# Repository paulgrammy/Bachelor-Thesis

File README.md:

# Bachelor-Thesis

## Introduction and motivation
In recent years, there has been a growing emphasis on learning through hands-on experimentation, particularly in engineering education. One effective way to explore the behavior of electrical components is by using sound signals, which provide an intuitive and immediate way to observe phenomena such as filtering and waveshaping. \newline

My body of work builds on my prior student research project that exemplified this approach using filters. In the project, a prototype was built that takes Bluetooth audio from a source and feeds it through filters studied in electronics labs, thus enabling a better understanding of signal processing concepts. The board then passes the resulting sound to an audio device such as headphones or speakers.

## Requirements and considerations
System-wise, the board shall take +15 V and step it down to supply voltages required by each IC. A 2-layered design is shown, featuring four mounting pins for FestoBoard compatibility. Below, a block diagram is shown, underlying the ICs used for my implementation:

## Physical view
SMD components alongside SOIC packages for ICs have been used to allow space for all components. Alongside passives and ICs, some buttons and LEDs have been added for user interaction. These shall be handled by the ESP32:

## Software
The ESP32 found on the PCB acts as either:
1) A Bluetooth receiver using [pschatzmann's A2DP library](https://github.com/pschatzmann/ESP32-A2DP);
2) A waveform generator, interfacing via I2S with the DAC to output one of four different waveforms.

FreeRTOS tasks are used to handle the different states of the code:

## Repo structure
* doc: Pictures, Datasheets, Files documenting different aspects of the project
* footprints: different footprints used in the PCB layout
* schematics: KiCAD schematic and layout, and the LTSpice simulation of Op-Amp stages can be found here
* software: the code implementation

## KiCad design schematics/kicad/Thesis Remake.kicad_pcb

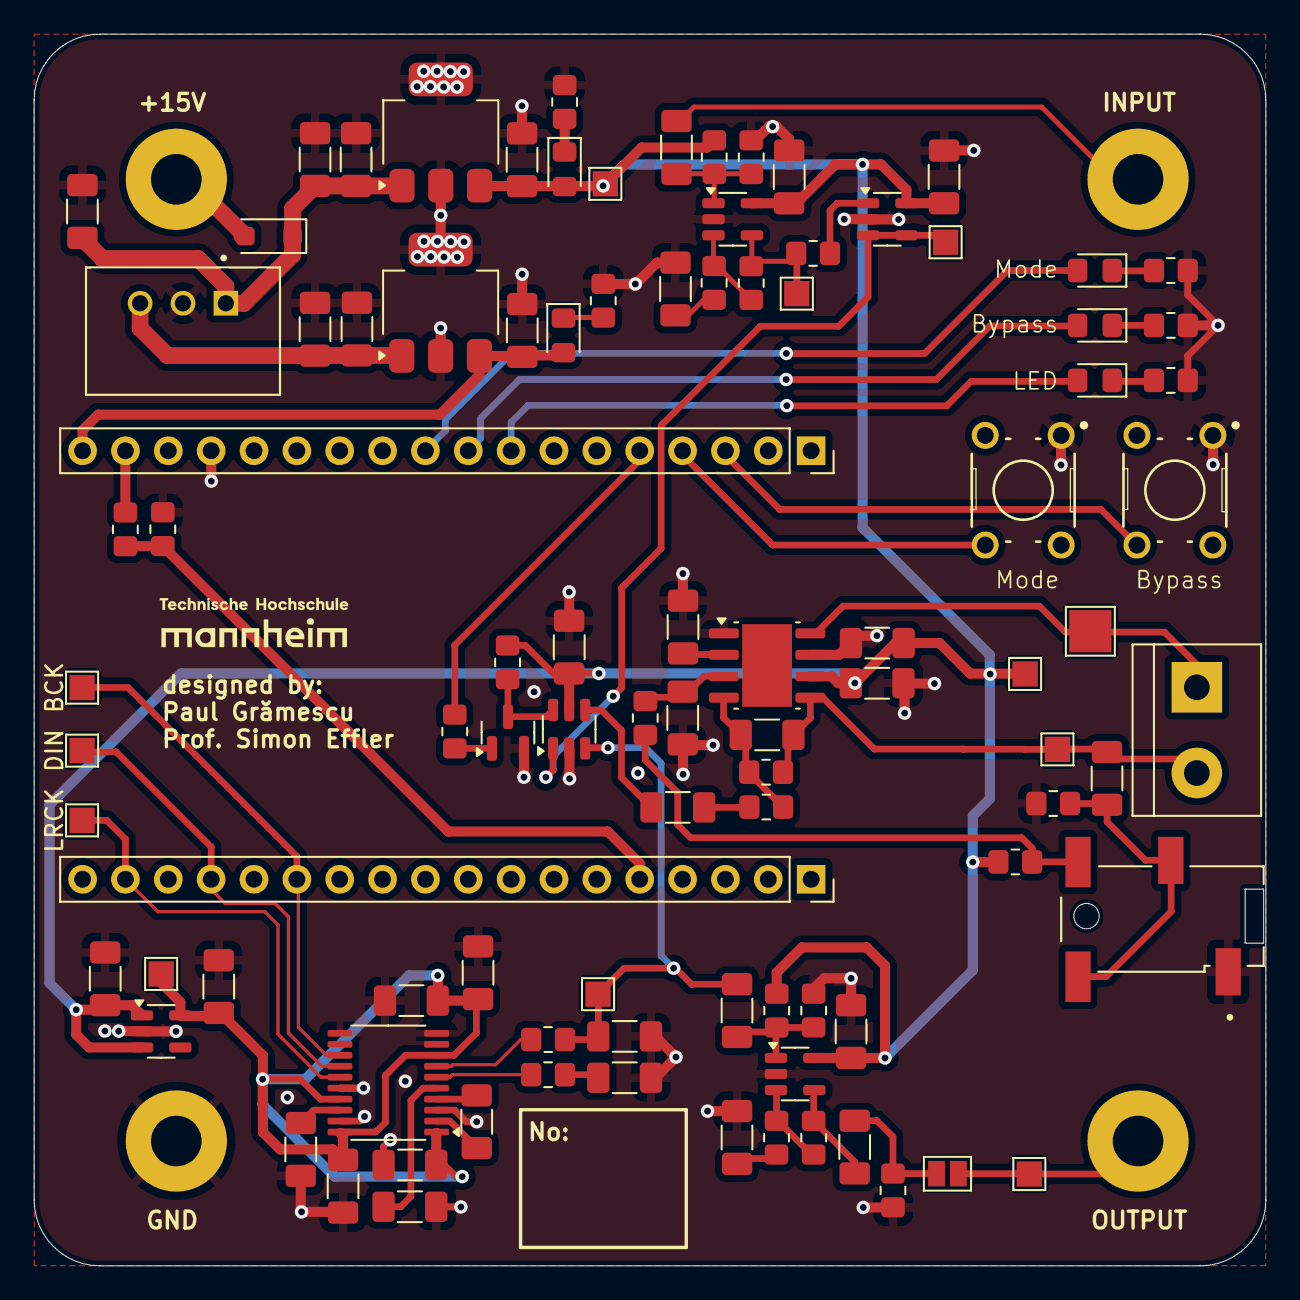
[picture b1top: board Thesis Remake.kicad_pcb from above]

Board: 2 copper layers, 73.0 x 73.0 mm, 100 parts (0 on the bottom side), 55 nets.

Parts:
+5V1: TestPoint; TestPoint_Pad_1.5x1.5mm
BCK: TestPoint; TestPoint_Pad_1.5x1.5mm
BUFFER_OUT1: TestPoint; TestPoint_Pad_1.5x1.5mm
C1, C4, C11, C17, C19, C20, C21, C24, C27, C30, C34: 10uF; C_1206_3216Metric_Pad1.33x1.80mm_HandSolder
C2, C5, C33: 0.47uF; C_1206_3216Metric_Pad1.33x1.80mm_HandSolder
C3, C6, C8: 22uF; C_1206_3216Metric_Pad1.33x1.80mm_HandSolder
C7: 1uF; C_1206_3216Metric_Pad1.33x1.80mm_HandSolder
C9, C10: 2.2nF; C_1206_3216Metric_Pad1.33x1.80mm_HandSolder
C12, C13, C15, C16, C26, C28: 0.1uF; C_1206_3216Metric_Pad1.33x1.80mm_HandSolder
C14, C25, C32: 2.2uF; C_1206_3216Metric_Pad1.33x1.80mm_HandSolder
C18, C22, C23, C31: 10nF; C_1206_3216Metric_Pad1.33x1.80mm_HandSolder
C29: 5pF; C_1206_3216Metric_Pad1.33x1.80mm_HandSolder
D5: D_Schottky; D_SOD-123F
D7, D8, D9, D10, D11: LED; LED_0805_2012Metric_Pad1.15x1.40mm_HandSolder
DEBUG1: 0; R_0805_2012Metric_Pad1.20x1.40mm_HandSolder
DIN: TestPoint; TestPoint_Pad_1.5x1.5mm
J1: SJ2-35853B-SMT-TR; CUI_SJ2-35853B-SMT-TR
J2, J3: Conn_01x18; PinSocket_1x18_P2.54mm_Vertical
J4, J5, J6, J7: Conn_01x01_Pin; FestoBoard_Drill_Hole
JP3: Jumper_2_Open; SolderJumper-2_P1.3mm_Open_Pad1.0x1.5mm
LRCK: TestPoint; TestPoint_Pad_1.5x1.5mm
LS1: Speaker; TerminalBlock_bornier-2_P5.08mm
OUTPUT_AS1, OUTPUT_AS2: TestPoint; TestPoint_Pad_1.5x1.5mm
OUT_DAC_R1: TestPoint; TestPoint_Pad_1.5x1.5mm
PS1: TSR_0.5-2465; CONV_TSR_0.5-2465
Q1: MMBT7002K; SOT-23
R1, R2: 330; R_0805_2012Metric_Pad1.20x1.40mm_HandSolder
R3, R4, R20: 470; R_0805_2012Metric_Pad1.20x1.40mm_HandSolder
R5, R6, R10, R11, R17: 10K; R_0805_2012Metric_Pad1.20x1.40mm_HandSolder
R7: 100k; R_0805_2012Metric_Pad1.20x1.40mm_HandSolder
R8, R13, R19: 5K; R_0805_2012Metric_Pad1.20x1.40mm_HandSolder
R9, R12, R14, R15: 100K; R_0805_2012Metric_Pad1.20x1.40mm_HandSolder
R16: 50k; R_0805_2012Metric_Pad1.20x1.40mm_HandSolder
R18: 1K; R_0805_2012Metric_Pad1.20x1.40mm_HandSolder
R21, R22: 1k; R_0805_2012Metric_Pad1.20x1.40mm_HandSolder
R23, R24, R25: 2.2K; R_0805_2012Metric_Pad1.20x1.40mm_HandSolder
S1, S2: B3F-1000; SW_B3F-1000
TP_VDD_TPA1: TestPoint; TestPoint_Pad_1.5x1.5mm
U2: PCM5102; TSSOP-20_4.4x6.5mm_P0.65mm
U3: SN74LVC1G3157; SOT-23-6
U5: RT9080-33GJ5; SOT-23-5
U6, U8: LM2940CT-5.0_MOD; SOT-223
U7: TPA711; Texas_R-PDSO-G8_EP2.95x4.9mm_Mask2.4x3.1mm
U9, U10, U11: MCP6001-OT; SOT-23-5
VDD1: TestPoint; TestPoint_Pad_1.5x1.5mm
Vo+1: TestPoint; TestPoint_Pad_1.5x1.5mm
Vo-1: TestPoint; TestPoint_Pad_2.5x2.5mm

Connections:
+3v3: C8.2, C11.1, C12.2, C13.2, C15.2, U2.1 (CPVDD), U2.8 (AVDD), U2.17 (XSMT), U2.20 (DVDD), U5.5 (VOUT), VDD1.1
+3v3_ESP: J2.17, R21.2
+5V: +5V1.1, C3.2, C7.2, C18.2, C22.2, C23.2, C27.1, C28.1, C31.1, D10.2 (A), R5.2, R10.2, R15.2, R19.2, TP_VDD_TPA1.1, U3.5 (+), U5.1 (VIN), U5.3 (EN), U7.6 (V_{DD}), U8.3 (OUT), U9.5 (V+), U10.5 (V+), U11.5 (V+)
+5V1: C6.2, D11.2 (A), J2.18, U6.3 (OUT)
+6.5V: C4.1, C5.2, PS1.3 (+VOUT), U6.1 (IN)
+15V: D5.2 (A), J5.1
+15V_Diode: C1.1, C2.2, C34.1, D5.1 (K), PS1.1 (+VIN), U8.1 (IN)
/ADC: J3.5, R21.1, R22.1
/BCK: BCK.1, J3.13, U2.13 (BCK)
/BUFFEROUT: BUFFER_OUT1.1, U3.1 (B), U11.3 (-), U11.4
/Bypass: C33.2, U3.4 (C)
/DIN: DIN.1, J3.15, U2.14 (DIN)
/Filter_IN: J7.1, JP3.2 (B), OUTPUT_AS1.1
/Filter_OUT: C21.1, J6.1
/HI_LO: J2.5, R20.1
/IN: C29.1, R16.2, R17.2, U7.4 (IN)
/LDOO: C16.1, U2.18 (LDOO)
/LED_1: D7.2 (A), J2.8
/LED_2: D8.2 (A), J2.9
/LED_3: D9.2 (A), J2.10
/LRCK: J3.17, LRCK.1, U2.15 (LRCK)
/OUTDACL: C9.1, R3.2
/OUTDACR: C10.1, C17.1, OUT_DAC_R1.1, R4.2, U3.3 (A)
/Poll_Button_1: J2.4, S1.4
/Poll_Button_2: J2.3, S2.4
/SE/~BTL: J1.10, R14.1, R15.1
/VNEG: C14.2, U2.5 (VNEG)
/Vo+: C29.2, C30.1, LS1.2, R16.1, U7.5 (V_{O+}), Vo+1.1
/Vo-: LS1.1, U7.8 (V_{O-}), Vo-1.1
GND: C1.2, C2.1, C3.1, C4.2, C5.1, C6.1, C7.1, C8.1, C9.2, C10.2, C11.2, C12.1, C13.1, C14.1, C15.1, C16.2, C18.1, C20.1, C22.1, C23.1, C24.1, C25.2, C26.2, C27.2, C28.2, C31.2, C34.2, J1.1, J2.15, J4.1, PS1.2 (GND), Q1.2, R1.1, R2.1, R6.2, R9.1, R11.2, R18.2, R22.2, R23.1, R24.1, R25.1, S1.1, S2.1, U2.3 (CPGND), U2.9 (AGND), U2.10 (DEMP), U2.11 (FLT), U2.16 (FMT), U2.19 (DGND), U3.2 (-), U5.2 (GND), U6.2 (GND), U6.4 (GND), U7.1 (SHUTDOWN), U7.7 (GND), U8.2 (GND), U8.4 (GND), U9.2 (V-), U10.2 (V-), U11.2 (V-)
unnamed: C19.2, R8.2, U9.4
unnamed: C20.2, R7.1
unnamed: C24.2, R12.1
unnamed: C30.2, J1.2, J1.3, R18.1
unnamed: C33.1, R17.1
unnamed: D7.1 (K), R23.2
unnamed: D8.1 (K), R24.2
unnamed: D9.1 (K), R25.2
unnamed: D10.1 (K), R1.2
unnamed: D11.1 (K), R2.2
unnamed: DEBUG1.1, OUTPUT_AS2.1, R13.2, U10.4
unnamed: C19.1, JP3.1 (A), R9.2
unnamed: Q1.1, R20.2
unnamed: C32.2, U2.4 (CAPM)
unnamed: C32.1, U2.2 (CAPP)
unnamed: R3.1, U2.6 (OUTL)
unnamed: R4.1, U2.7 (OUTR)
unnamed: Q1.3, R19.1, U3.6 (S)
unnamed: C25.1, U7.2 (BYPASS)
unnamed: C26.1, R14.2, U7.3 (SE/~BTL)
unnamed: C17.2, R5.1, R6.1, U9.1 (+)
unnamed: R7.2, R8.1, U9.3 (-)
unnamed: C21.2, R10.1, R11.1, U10.1 (+)
unnamed: R12.2, R13.1, U10.3 (-)
unnamed: DEBUG1.2, U11.1 (+)

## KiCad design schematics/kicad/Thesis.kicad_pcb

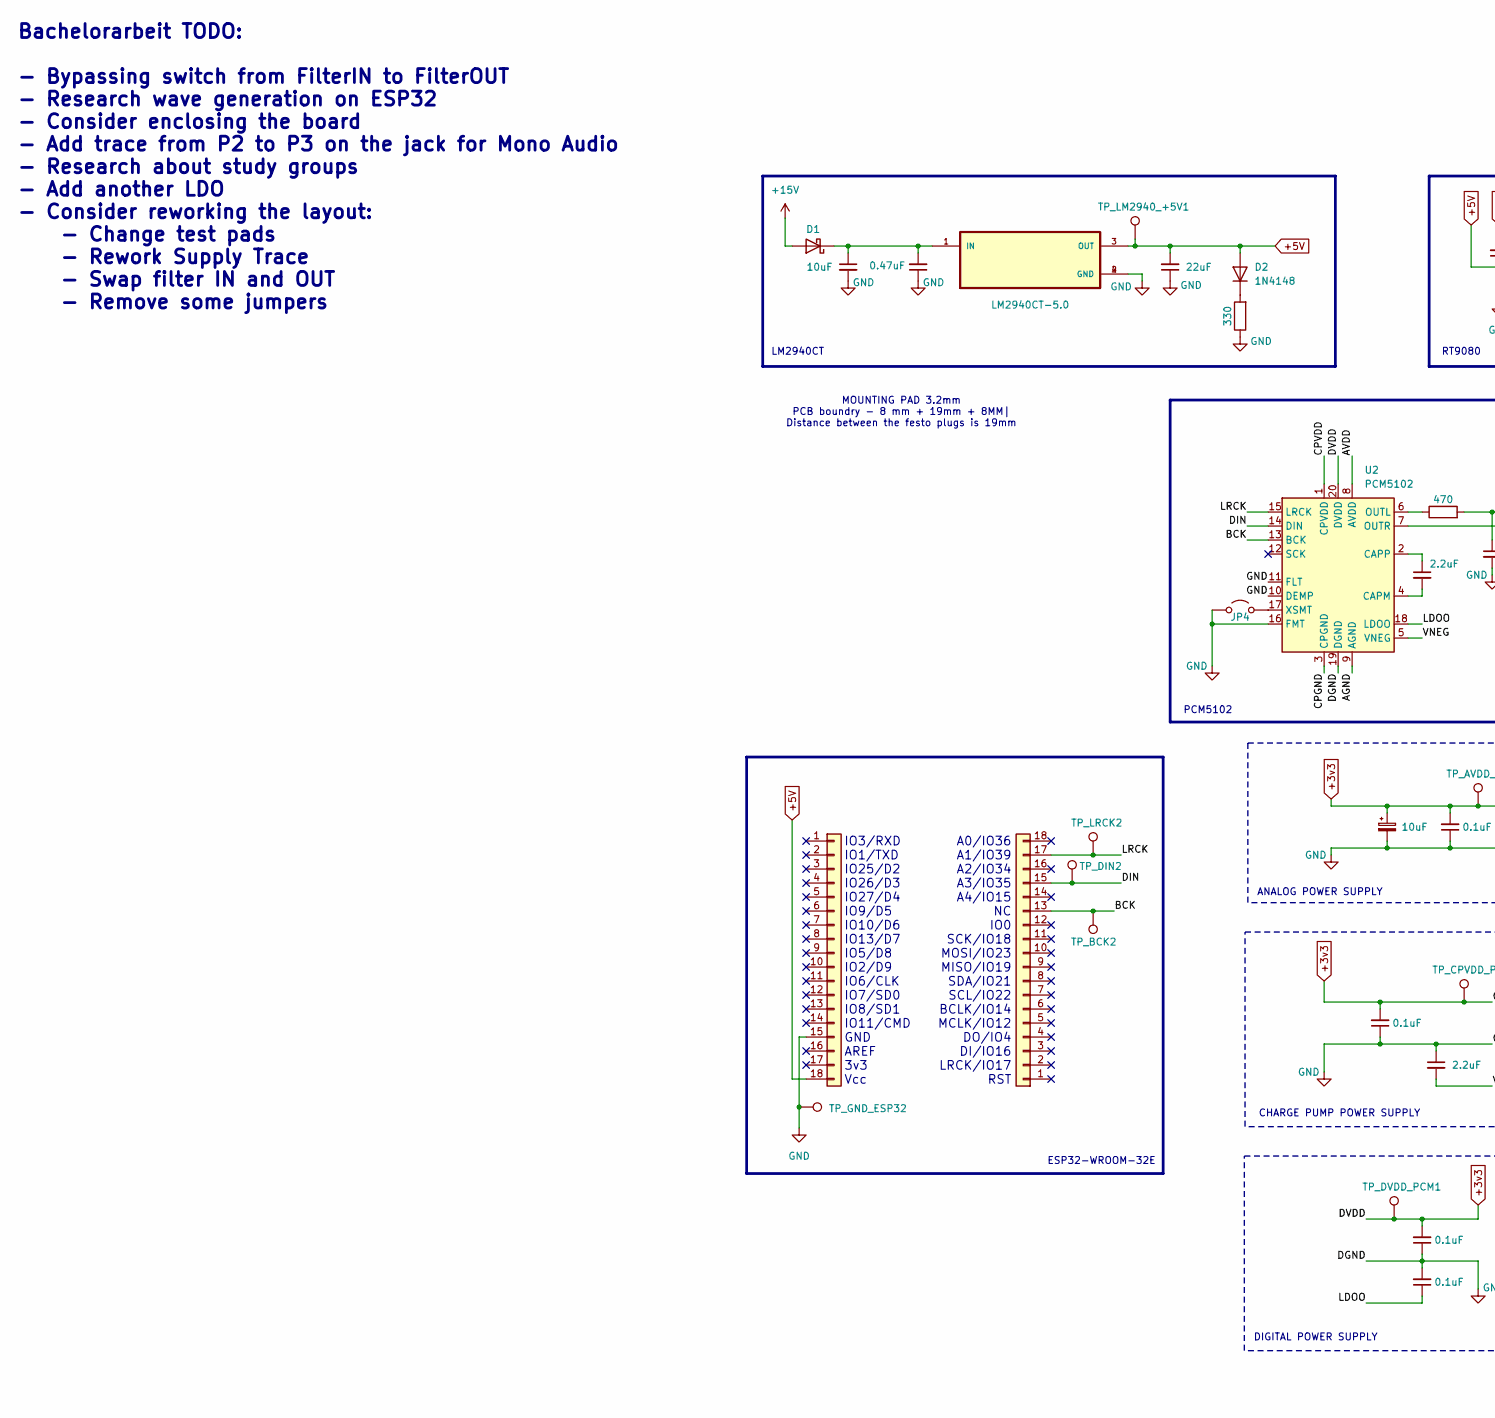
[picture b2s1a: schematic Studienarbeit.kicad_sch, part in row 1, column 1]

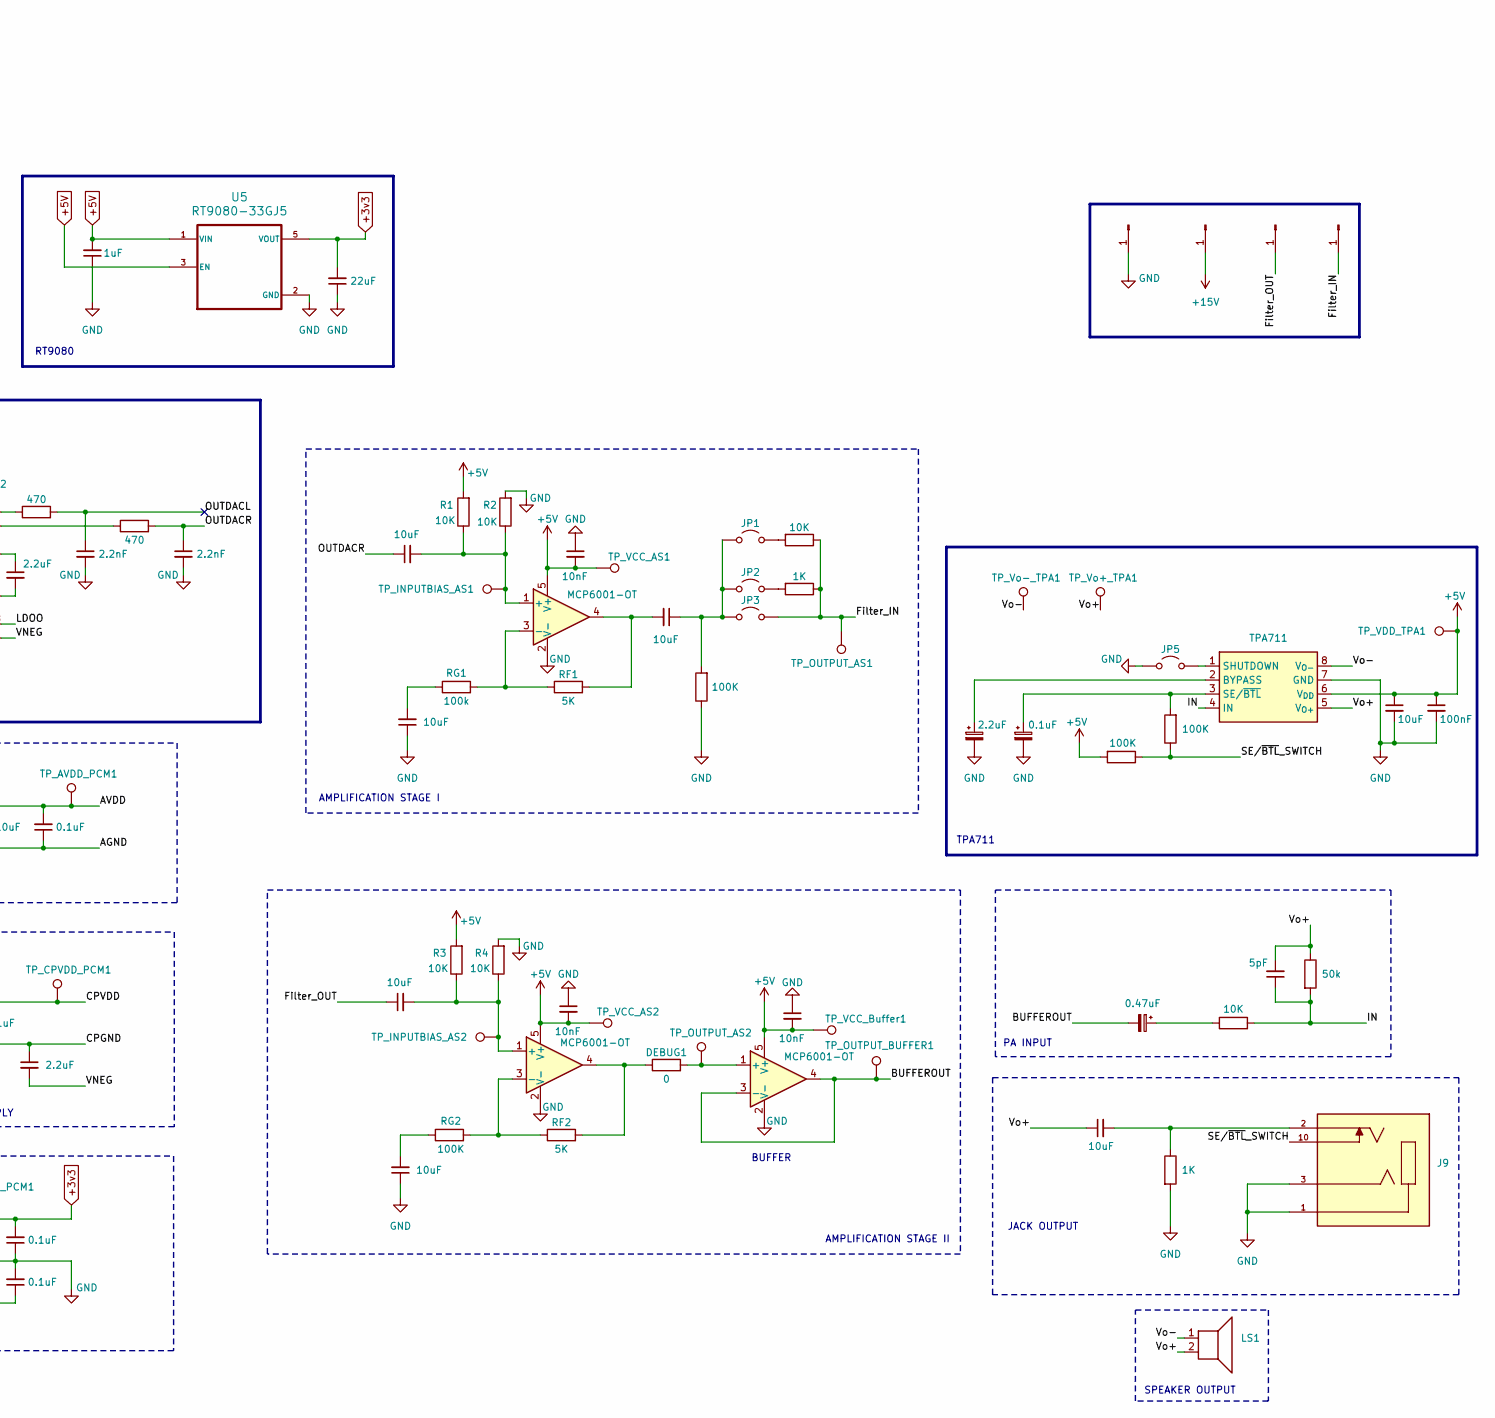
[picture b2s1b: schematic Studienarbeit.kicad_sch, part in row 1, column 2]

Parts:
C1_APS_PCM5102: 10uF; C_1206_3216Metric_Pad1.33x1.80mm_HandSolder
C1_CPPS_PCM1, C1_DPS_PCM1, C2_APS_PCM5102, C2_DPS_PCM1: 0.1uF; C_1206_3216Metric_Pad1.33x1.80mm_HandSolder
C2_CPPS_PCM1: 2.2uF; C_1206_3216Metric_Pad1.33x1.80mm_HandSolder
CA_PCM5102: 2.2uF; C_1206_3216Metric_Pad1.33x1.80mm_HandSolder
CB_TPA1: 2.2uF; C_1206_3216Metric_Pad1.33x1.80mm_HandSolder
CF_TPA711: 5pF; C_1206_3216Metric_Pad1.33x1.80mm_HandSolder
CG1_PCM5102, CG2_PCM5102: 2.2nF; C_1206_3216Metric_Pad1.33x1.80mm_HandSolder
CI_TPA711: 0.47uF; C_1206_3216Metric_Pad1.33x1.80mm_HandSolder
C_COUPLING_AMPSTAGE1: 10uF; C_1206_3216Metric_Pad1.33x1.80mm_HandSolder
C_COUPLING_AMPSTAGE2, C_COUPLING_AMPSTAGE3, C_COUPLING_AMPSTAGE4: 10nF; C_1206_3216Metric_Pad1.33x1.80mm_HandSolder
C_GND_AMPSTAGE1, C_GND_AMPSTAGE2, C_GND_AMPSTAGE3: 10uF; C_1206_3216Metric_Pad1.33x1.80mm_HandSolder
C_INPUT_LDO1: 0.47uF; C_1206_3216Metric_Pad1.33x1.80mm_HandSolder
C_INPUT_RT1: 22uF; C_1206_3216Metric_Pad1.33x1.80mm_HandSolder
C_INPUT_RT9080: 1uF; C_1206_3216Metric_Pad1.33x1.80mm_HandSolder
C_INPUT_TPA1, C_INPUT_TPA3: 10uF; C_1206_3216Metric_Pad1.33x1.80mm_HandSolder
C_INPUT_TPA2: 100nF; C_1206_3216Metric_Pad1.33x1.80mm_HandSolder
C_IN_+15V_1: 10uF; C_1206_3216Metric_Pad1.33x1.80mm_HandSolder
C_IN_AMPSTAGE1: 10uF; C_1206_3216Metric_Pad1.33x1.80mm_HandSolder
C_OUTPUT_LDO1: 22uF; C_1206_3216Metric_Pad1.33x1.80mm_HandSolder
C_SE/BTL_TPA1: 0.1uF; C_1206_3216Metric_Pad1.33x1.80mm_HandSolder
D1: D_Schottky; D_SOD-123F
D2: 1N4148; D_SOD-123F
DEBUG1: 0; R_0805_2012Metric_Pad1.20x1.40mm_HandSolder
J2, J3: Conn_01x18; PinSocket_1x18_P2.54mm_Vertical
J4, J5, J6, J7: Conn_01x01_Pin; FestoBoard_Drill_Hole
J9: SJ2-35853B-SMT-TR; CUI_SJ2-35853B-SMT-TR; PARTREV 1.04
JP1, JP2, JP3, JP4, JP5: Jumper_2_Open; SolderJumper-2_P1.3mm_Open_Pad1.0x1.5mm
LS1: Speaker; TerminalBlock_bornier-2_P5.08mm
R1, R2, R3, R4: 10K; R_0805_2012Metric_Pad1.20x1.40mm_HandSolder
R11: 1K; R_0805_2012Metric_Pad1.20x1.40mm_HandSolder
R12, R13: 100K; R_0805_2012Metric_Pad1.20x1.40mm_HandSolder
RF1, RF2: 5K; R_0805_2012Metric_Pad1.20x1.40mm_HandSolder
RF_TPA711: 50k; R_0805_2012Metric_Pad1.20x1.40mm_HandSolder
RG1: 100k; R_0805_2012Metric_Pad1.20x1.40mm_HandSolder
RG2: 100K; R_0805_2012Metric_Pad1.20x1.40mm_HandSolder
RI_TPA711: 10K; R_0805_2012Metric_Pad1.20x1.40mm_HandSolder
ROUTDACL1: 470; R_0805_2012Metric_Pad1.20x1.40mm_HandSolder
ROUTDACR1: 470; R_0805_2012Metric_Pad1.20x1.40mm_HandSolder
R_COUPLING_AMPSTAGE1: 100K; R_0805_2012Metric_Pad1.20x1.40mm_HandSolder
R_COUPLING_AMPSTAGE2: 10K; R_0805_2012Metric_Pad1.20x1.40mm_HandSolder
R_COUPLING_AMPSTAGE3: 1K; R_0805_2012Metric_Pad1.20x1.40mm_HandSolder
STATUS_LED1: 330; R_0805_2012Metric_Pad1.20x1.40mm_HandSolder
TP_AVDD_PCM1: TestPoint; TestPoint_Pad_1.5x1.5mm
TP_BCK2: TestPoint; TestPoint_Pad_1.5x1.5mm
TP_CPVDD_PCM1: TestPoint; TestPoint_Pad_1.5x1.5mm
TP_DIN2: TestPoint; TestPoint_Pad_1.5x1.5mm
TP_DVDD_PCM1: TestPoint; TestPoint_Pad_1.5x1.5mm
TP_GND_ESP32: TestPoint; TestPoint_Pad_1.5x1.5mm
TP_INPUTBIAS_AS1, TP_INPUTBIAS_AS2: TestPoint; TestPoint_Pad_1.5x1.5mm
TP_LM2940_+5V1: TestPoint; TestPoint_Pad_1.5x1.5mm
TP_LRCK2: TestPoint; TestPoint_Pad_1.5x1.5mm
TP_OUTPUT_AS1, TP_OUTPUT_AS2: TestPoint; TestPoint_Pad_1.5x1.5mm
TP_OUTPUT_BUFFER1: TestPoint; TestPoint_Pad_1.5x1.5mm
TP_VCC_AS1, TP_VCC_AS2: TestPoint; TestPoint_Pad_1.5x1.5mm
TP_VCC_Buffer1: TestPoint; TestPoint_Pad_1.5x1.5mm
TP_VDD_TPA1: TestPoint; TestPoint_Pad_1.5x1.5mm
TP_Vo+_TPA1: TestPoint; TestPoint_Pad_1.5x1.5mm
TP_Vo-_TPA1: TestPoint; TestPoint_Pad_1.5x1.5mm
U1, U3, U4: MCP6001-OT; SOT95P270X145-5N
U2: PCM5102; TSSOP-20_4.4x6.5mm_P0.65mm
U5: RT9080-33GJ5; TSOT-23-5_RIT-L
U6: TPA711; Texas_R-PDSO-G8_EP2.95x4.9mm_Mask2.4x3.1mm
U7: LM2940CT-5.0; SOT-223

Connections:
+3v3: C1_APS_PCM5102.1, C1_CPPS_PCM1.2, C1_DPS_PCM1.2, C2_APS_PCM5102.2, C_INPUT_RT1.2, TP_AVDD_PCM1.1, TP_CPVDD_PCM1.1, TP_DVDD_PCM1.1, U2.1 (CPVDD), U2.8 (AVDD), U2.20 (DVDD), U5.5 (VOUT)
+5V: C_COUPLING_AMPSTAGE2.2, C_COUPLING_AMPSTAGE3.2, C_COUPLING_AMPSTAGE4.2, C_INPUT_RT9080.2, C_INPUT_TPA1.1, C_INPUT_TPA2.1, C_OUTPUT_LDO1.2, D2.2 (A), J2.18, R1.2, R3.2, R12.2, TP_LM2940_+5V1.1, TP_VCC_AS1.1, TP_VCC_AS2.1, TP_VCC_Buffer1.1, TP_VDD_TPA1.1, U1.5 (V+), U3.5 (V+), U4.5 (V+), U5.1 (VIN), U5.3 (EN), U6.6 (V_{DD}), U7.3 (OUT)
+15V: D1.2 (A), J5.1
/BCK: J3.13, TP_BCK2.1, U2.13 (BCK)
/BUFFEROUT: CI_TPA711.2, TP_OUTPUT_BUFFER1.1, U3.3 (-), U3.4
/DIN: J3.15, TP_DIN2.1, U2.14 (DIN)
/Filter_IN: J7.1, JP3.2 (B), R_COUPLING_AMPSTAGE2.1, R_COUPLING_AMPSTAGE3.1, TP_OUTPUT_AS1.1
/Filter_OUT: C_IN_AMPSTAGE1.1, J6.1
/IN: CF_TPA711.1, RF_TPA711.2, RI_TPA711.2, U6.4 (IN)
/LDOO: C2_DPS_PCM1.1, U2.18 (LDOO)
/LRCK: J3.17, TP_LRCK2.1, U2.15 (LRCK)
/OUTDACL: CG1_PCM5102.1, ROUTDACL1.2
/OUTDACR: CG2_PCM5102.1, C_GND_AMPSTAGE3.1, ROUTDACR1.2
/SE/~BTL_SWITCH: J9.10, R12.1, R13.1
/VNEG: C2_CPPS_PCM1.2, U2.5 (VNEG)
/Vo+: CF_TPA711.2, C_INPUT_TPA3.1, LS1.2, RF_TPA711.1, TP_Vo+_TPA1.1, U6.5 (V_{O+})
/Vo-: LS1.1, TP_Vo-_TPA1.1, U6.8 (V_{O-})
GND: C1_APS_PCM5102.2, C1_CPPS_PCM1.1, C1_DPS_PCM1.1, C2_APS_PCM5102.1, C2_CPPS_PCM1.1, C2_DPS_PCM1.2, CB_TPA1.2, CG1_PCM5102.2, CG2_PCM5102.2, C_COUPLING_AMPSTAGE2.1, C_COUPLING_AMPSTAGE3.1, C_COUPLING_AMPSTAGE4.1, C_GND_AMPSTAGE1.1, C_GND_AMPSTAGE2.1, C_INPUT_LDO1.1, C_INPUT_RT1.1, C_INPUT_RT9080.1, C_INPUT_TPA1.2, C_INPUT_TPA2.2, C_IN_+15V_1.2, C_OUTPUT_LDO1.1, C_SE/BTL_TPA1.2, J2.15, J4.1, J9.1, J9.3, JP4.1 (A), JP5.1 (A), R2.2, R4.2, R11.2, R_COUPLING_AMPSTAGE1.1, STATUS_LED1.1, TP_GND_ESP32.1, U1.2 (V-), U2.3 (CPGND), U2.9 (AGND), U2.10 (DEMP), U2.11 (FLT), U2.16 (FMT), U2.19 (DGND), U3.2 (V-), U4.2 (V-), U5.2 (GND), U6.7 (GND), U7.2 (GND), U7.4 (GND)
unnamed: CI_TPA711.1, RI_TPA711.1
unnamed: C_COUPLING_AMPSTAGE1.2, RF1.2, U4.4
unnamed: C_GND_AMPSTAGE1.2, RG1.1
unnamed: C_GND_AMPSTAGE2.2, RG2.1
unnamed: C_INPUT_TPA3.2, J9.2, R11.1
unnamed: C_INPUT_LDO1.2, C_IN_+15V_1.1, D1.1 (K), U7.1 (IN)
unnamed: D2.1 (K), STATUS_LED1.2
unnamed: DEBUG1.1, RF2.2, U1.4
unnamed: C_COUPLING_AMPSTAGE1.1, JP1.1 (A), JP2.1 (A), JP3.1 (A), R_COUPLING_AMPSTAGE1.2
unnamed: JP1.2 (B), R_COUPLING_AMPSTAGE2.2
unnamed: JP2.2 (B), R_COUPLING_AMPSTAGE3.2
unnamed: JP4.2 (B), U2.17 (XSMT)
unnamed: JP5.2 (B), U6.1 (SHUTDOWN)
unnamed: C_IN_AMPSTAGE1.2, R3.1, R4.1, TP_INPUTBIAS_AS2.1, U1.1 (+)
unnamed: RF2.1, RG2.2, U1.3 (-)
unnamed: CA_PCM5102.2, U2.4 (CAPM)
unnamed: CA_PCM5102.1, U2.2 (CAPP)
unnamed: ROUTDACL1.1, U2.6 (OUTL)
unnamed: ROUTDACR1.1, U2.7 (OUTR)
unnamed: DEBUG1.2, TP_OUTPUT_AS2.1, U3.1 (+)
unnamed: C_GND_AMPSTAGE3.2, R1.1, R2.1, TP_INPUTBIAS_AS1.1, U4.1 (+)
unnamed: RF1.1, RG1.2, U4.3 (-)
unnamed: CB_TPA1.1, U6.2 (BYPASS)
unnamed: C_SE/BTL_TPA1.1, R13.2, U6.3 (SE/~BTL)

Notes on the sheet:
PCM5102
CHARGE PUMP POWER SUPPLY
PA INPUT
Bachelorarbeit TODO: - Bypassing switch from FilterIN to FilterOUT - Research wave generation on ESP32 - Consider enclosing the board - Add trace from P2 to P3 on the jack for Mono Audio - Research about study groups - Add another LDO - Consider reworking the layout: - Change test pads - Rework Sup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
LM2940CT
TPA711
AMPLIFICATION STAGE II
ESP32-WROOM-32E
MOUNTING PAD 3.2mm PCB boundry - 8 mm + 19mm + 8MM| Distance between the festo plugs is 19mm
SPEAKER OUTPUT
A0/IO36 A1/IO39 A2/IO34 A3/IO35 A4/IO15 NC IO0 SCK/IO18 MOSI/IO23 MISO/IO19 SDA/IO21 SCL/IO22 BCLK/IO14 MCLK/IO12 DO/IO4 DI/IO16 LRCK/IO17 RST
JACK OUTPUT
RT9080
ANALOG POWER SUPPLY
IO3/RXD IO1/TXD IO25/D2 IO26/D3 IO27/D4 IO9/D5 IO10/D6 IO13/D7 IO5/D8 IO2/D9 IO6/CLK IO7/SD0 IO8/SD1 IO11/CMD GND AREF 3v3 Vcc
BUFFER
DIGITAL POWER SUPPLY
AMPLIFICATION STAGE I

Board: 2 copper layers, 81 parts (0 on the bottom side), 40 nets, no tracks yet.

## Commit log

2025-03-31 Couple of imports from Student-Research.
2025-03-31 Added PCB file.
2025-04-21 Added LED blinking to test later on HW.
2025-04-26 Commits
2025-05-13 code commits
2025-05-13 The intended state machine works, need to program waveshaping.
2025-05-21 Bluetooth works. Waveform generation glitches due to continuous generation.
2025-05-21 Bluetooth works. Waveform generation works.
2025-06-10 Commits for LUT
2025-06-10 Uneori nu inteleg de ce folosesc GitHub....
2025-06-16 QOL PCB changes
2025-06-16 Moved the buttons one pin lower to avoid TX
2025-06-16 Backup
2025-06-17 Implemented LUTs, need to debug
2025-06-17 Moved bypass switch from Pin 25 to 27 temp
2025-06-20 Updated PCB.
2025-06-20 Added the TH Logo on the board.
2025-06-20 LUT Works now.
2025-06-21 Updated schematic in main
2025-06-21 Added separate phase increments for the infected waveform.
2025-06-21 Using correct LED pins now.
2025-07-07 Reformatted code for easier reading.
2025-07-07 Ignore backups
2025-07-08 Pictures
2025-07-09 Added Focus Group task sheet.
2025-07-09 Added the task sheet in main too.
2025-08-07 Backups
2025-08-11 Changed to default pins
